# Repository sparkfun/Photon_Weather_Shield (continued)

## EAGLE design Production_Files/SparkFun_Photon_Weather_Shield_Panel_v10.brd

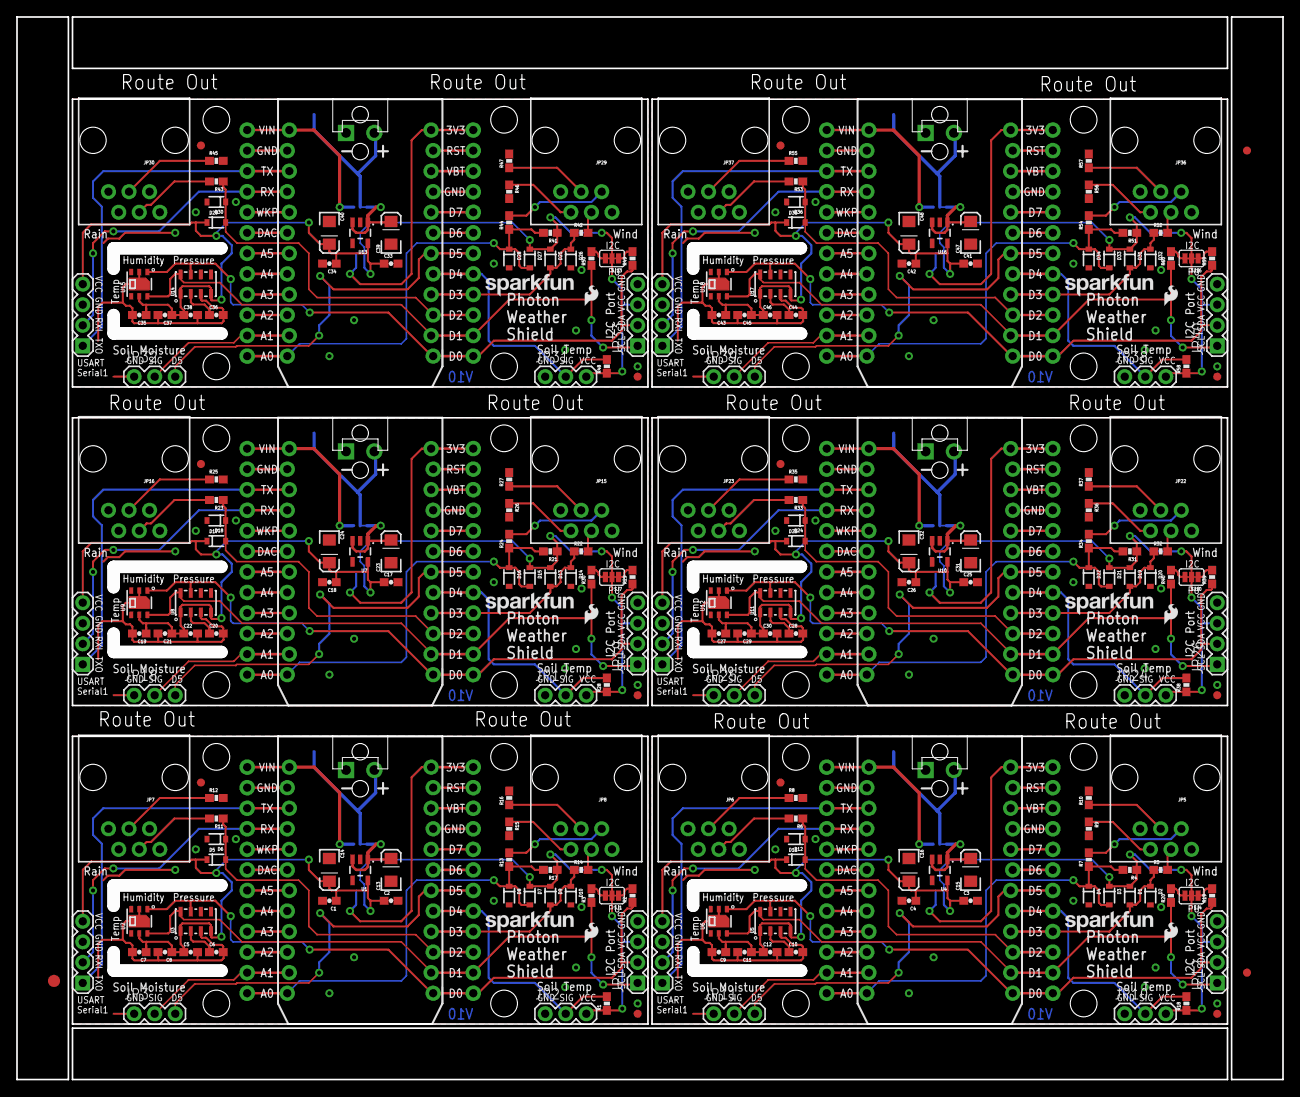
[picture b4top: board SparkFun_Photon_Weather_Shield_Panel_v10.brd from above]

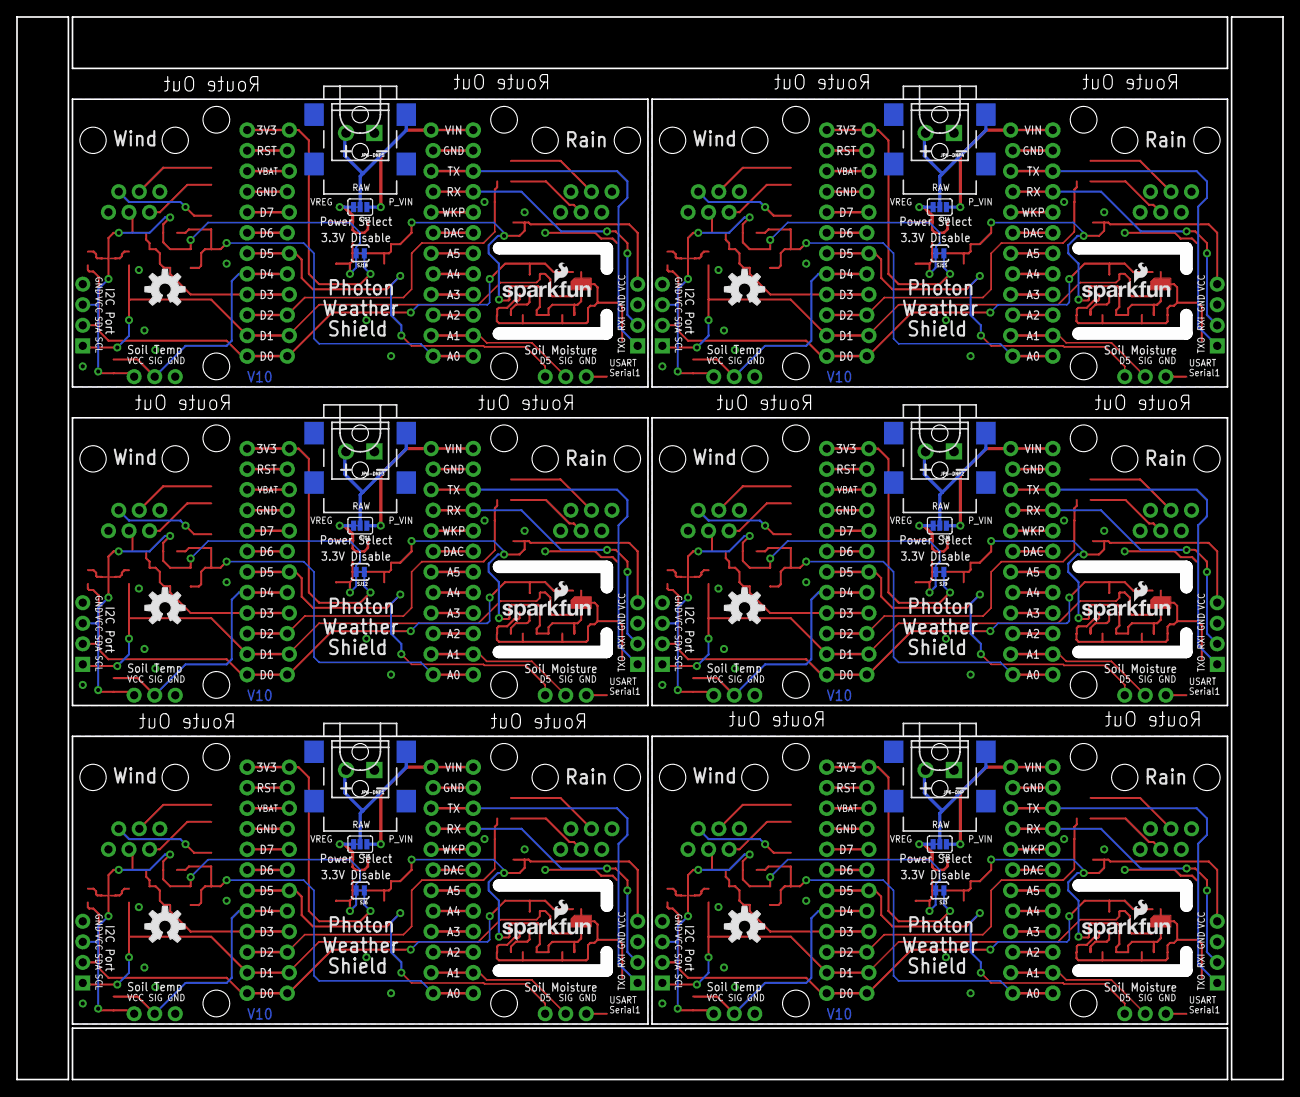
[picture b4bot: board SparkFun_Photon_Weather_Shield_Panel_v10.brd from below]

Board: 2 copper layers, 155.1 x 130.0 mm, 273 parts (36 on the bottom side), 150 nets.

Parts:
C1, C4, C8, C11, C18, C21, C26, C29, C34, C37, C42, C45: 1.0uF; 0603-CAP
C2, C3, C5, C6, C7, C9, C10, C12, C17, C19, C20, C22, C25, C27, C28, C30, C33, C35, C36, C38, C41, C43, C44, C46: 0.1uF; 0603-CAP
C13, C14, C15, C16, C23, C24, C31, C32, C39, C40, C47, C48: 10uF; EIA3216
D1, D2, D3, D4, D5, D6, D7, D8, D9, D10, D11, D12, D13, D14, D15, D16, D17, D18, D19, D20, D21, D22, D23, D24, D25, D26, D27, D28, D29, D30, D31, D32, D33, D34, D35, D36: 250mA/100V; SOD-323
E$1: FIDUCIAL-1.5X3
E$3, E$4: FIDUCIAL-1X2
FID1, FID2, FID3, FID4, FID5, FID6, FID7, FID8, FID9, FID10, FID11, FID12: FIDUCIAL1X2; FIDUCIAL-1X2
JP1, JP12, JP19, JP26, JP33, JP40: I2C Port; 1X04
JP2, JP10, JP17, JP24, JP31, JP38: Soil/Water Temp; 1X03
JP3, JP11, JP18, JP25, JP32, JP39: Soil Moisture; 1X03
JP4, JP13, JP20, JP27, JP34, JP41: Serial1 Port; 1X04
JP5, JP6, JP7, JP8, JP15, JP16, JP22, JP23, JP29, JP30, JP36, JP37: RJ11; RJ11-6
JP5-DNP, JP5-DNP1, JP5-DNP2, JP5-DNP3, JP5-DNP4, JP5-DNP5: 5.5x2.1mm Barrel; POWER_JACK_SMD
JP6-DNP, JP6-DNP1, JP6-DNP2, JP6-DNP3, JP6-DNP4, JP6-DNP5: SCREWTERMINAL-3.5MM-2
JP9, JP14, JP21, JP28, JP35, JP42: PHOTON_TEMPLATE_WIDE_LOCKING; SPARK_PHOTON_TEMPLATE_WIDE_LOCKING
LOGO1, LOGO3, LOGO5, LOGO7, LOGO9, LOGO11: OSHW-LOGOM; OSHW-LOGO-M
LOGO2, LOGO4, LOGO6, LOGO8, LOGO10, LOGO12: SFE_LOGO_NAME.1_INCH; SFE_LOGO_NAME_.1
R1, R4, R17, R18, R21, R28, R31, R38, R41, R48, R51, R58: 4.7K; 0603-RES
R2, R3, R19, R20, R29, R30, R39, R40, R49, R50, R59, R60: 10K; 0603-RES
R5, R6, R7, R8, R9, R10, R11, R12, R13, R14, R15, R16, R22, R23, R24, R25, R26, R27, R32, R33, R34, R35, R36, R37, R42, R43, R44, R45, R46, R47, R52, R53, R54, R55, R56, R57: 1K; 0603-RES
SJ1, SJ4, SJ7, SJ10, SJ13, SJ16: PAD-JUMPER-3-3OF3_NC_BY_TRACE_YES_SILK_FULL_BOX
SJ2, SJ5, SJ8, SJ11, SJ14, SJ17: PAD-JUMPER-3-2OF3_NC_BY_TRACE_YES_SILK_FULL_BOX
SJ3, SJ6, SJ9, SJ12, SJ15, SJ18: PAD-JUMPER-2-NC_BY_TRACE_YES_SILK
U1, U4, U7, U10, U13, U16: 3.3V MIC5219; SOT23-5
U2, U6, U9, U12, U15, U18: HTU21D
U3, U5, U8, U11, U14, U17: MPL3115A2LGA8; LGA8
U$1, U$2, U$5, U$7, U$9, U$11: SFE_LOGO_NAME_FLAME_.1
U$3, U$4, U$6, U$8, U$10, U$12: SFE_LOGO_FLAME_.1

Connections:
3.3V: C1.1, C2.1, C5.1, C7.1, C8.1, C14.A, D5.C, D7.C, D9.C, JP1.3, JP2.3, JP4.4, R1.1, R17.1, SJ1.2, SJ3.2, U1.5, U2.VDD, U3.1, U3.4
3.3V1: C3.1, C4.1, C9.1, C11.1, C12.1, C16.A, D1.C, D3.C, D11.C, JP10.3, JP12.3, JP13.4, R4.1, R18.1, SJ4.2, SJ6.2, U4.5, U5.1, U5.4, U6.VDD
3.3V2: C17.1, C18.1, C19.1, C21.1, C22.1, C24.A, D13.C, D15.C, D17.C, JP17.3, JP19.3, JP20.4, R21.1, R28.1, SJ7.2, SJ9.2, U7.5, U8.1, U8.4, U9.VDD
3.3V3: C25.1, C26.1, C27.1, C29.1, C30.1, C32.A, D19.C, D21.C, D23.C, JP24.3, JP26.3, JP27.4, R31.1, R38.1, SJ10.2, SJ12.2, U10.5, U11.1, U11.4, U12.VDD
3.3V4: C33.1, C34.1, C35.1, C37.1, C38.1, C40.A, D25.C, D27.C, D29.C, JP31.3, JP33.3, JP34.4, R41.1, R48.1, SJ13.2, SJ15.2, U13.5, U14.1, U14.4, U15.VDD
3.3V5: C41.1, C42.1, C43.1, C45.1, C46.1, C48.A, D31.C, D33.C, D35.C, JP38.3, JP40.3, JP41.4, R51.1, R58.1, SJ16.2, SJ18.2, U16.5, U17.1, U17.4, U18.VDD
GND: C1.2, C2.2, C5.2, C6.2, C7.2, C8.2, C13.C, C14.C, D6.A, D8.A, D10.A, JP1.4, JP2.1, JP3.1, JP4.3, JP5-DNP.GND, JP5-DNP.P$4, JP6-DNP.1, JP9.2, JP9.21, JP9.GND@0, JP9.GND@2, R12.2, R15.2, R16.2, U1.2, U2.7, U2.GND, U3.3
GND1: C3.2, C4.2, C9.2, C10.2, C11.2, C12.2, C15.C, C16.C, D2.A, D4.A, D12.A, JP5-DNP1.GND, JP5-DNP1.P$4, JP6-DNP1.1, JP10.1, JP11.1, JP12.4, JP13.3, JP14.2, JP14.21, JP14.GND@0, JP14.GND@2, R8.2, R9.2, R10.2, U4.2, U5.3, U6.7, U6.GND
GND2: C17.2, C18.2, C19.2, C20.2, C21.2, C22.2, C23.C, C24.C, D14.A, D16.A, D18.A, JP5-DNP2.GND, JP5-DNP2.P$4, JP6-DNP2.1, JP17.1, JP18.1, JP19.4, JP20.3, JP21.2, JP21.21, JP21.GND@0, JP21.GND@2, R25.2, R26.2, R27.2, U7.2, U8.3, U9.7, U9.GND
GND3: C25.2, C26.2, C27.2, C28.2, C29.2, C30.2, C31.C, C32.C, D20.A, D22.A, D24.A, JP5-DNP3.GND, JP5-DNP3.P$4, JP6-DNP3.1, JP24.1, JP25.1, JP26.4, JP27.3, JP28.2, JP28.21, JP28.GND@0, JP28.GND@2, R35.2, R36.2, R37.2, U10.2, U11.3, U12.7, U12.GND
GND4: C33.2, C34.2, C35.2, C36.2, C37.2, C38.2, C39.C, C40.C, D26.A, D28.A, D30.A, JP5-DNP4.GND, JP5-DNP4.P$4, JP6-DNP4.1, JP31.1, JP32.1, JP33.4, JP34.3, JP35.2, JP35.21, JP35.GND@0, JP35.GND@2, R45.2, R46.2, R47.2, U13.2, U14.3, U15.7, U15.GND
GND5: C41.2, C42.2, C43.2, C44.2, C45.2, C46.2, C47.C, C48.C, D32.A, D34.A, D36.A, JP5-DNP5.GND, JP5-DNP5.P$4, JP6-DNP5.1, JP38.1, JP39.1, JP40.4, JP41.3, JP42.2, JP42.21, JP42.GND@0, JP42.GND@2, R55.2, R56.2, R57.2, U16.2, U17.3, U18.7, U18.GND
unnamed: JP8.3, R14.2
unnamed: JP8.2, R13.2
unnamed: R3.2, SJ1.3
unnamed: JP7.3, R11.2
unnamed: C6.1, U3.2
unnamed: R2.2, SJ1.1
unnamed: JP9.3V3, JP9.24, SJ3.1
unnamed: C10.1, U5.2
unnamed: JP5.2, R7.2
unnamed: JP5.3, R5.2
unnamed: JP7.4, R12.1
unnamed: JP8.5, R15.1
unnamed: JP8.4, R16.1
unnamed: JP6.3, R6.2
unnamed: JP6.4, R8.1
unnamed: JP5.5, R9.1
unnamed: JP5.4, R10.1
unnamed: R20.2, SJ4.3
unnamed: R19.2, SJ4.1
unnamed: JP14.3V3, JP14.24, SJ6.1
unnamed: C20.1, U8.2
unnamed: JP15.2, R24.2
unnamed: JP15.3, R22.2
unnamed: JP16.3, R23.2
unnamed: JP16.4, R25.1
unnamed: JP15.5, R26.1
unnamed: JP15.4, R27.1
unnamed: R30.2, SJ7.3
unnamed: R29.2, SJ7.1
unnamed: JP21.3V3, JP21.24, SJ9.1
unnamed: C28.1, U11.2
unnamed: JP22.2, R34.2
unnamed: JP22.3, R32.2
unnamed: JP23.3, R33.2
unnamed: JP23.4, R35.1
unnamed: JP22.5, R36.1
unnamed: JP22.4, R37.1
unnamed: R40.2, SJ10.3
unnamed: R39.2, SJ10.1
unnamed: JP28.3V3, JP28.24, SJ12.1
unnamed: C36.1, U14.2
unnamed: JP29.2, R44.2
unnamed: JP29.3, R42.2
unnamed: JP30.3, R43.2
unnamed: JP30.4, R45.1
unnamed: JP29.5, R46.1
unnamed: JP29.4, R47.1
unnamed: R50.2, SJ13.3
unnamed: R49.2, SJ13.1
unnamed: JP35.3V3, JP35.24, SJ15.1
unnamed: C44.1, U17.2
unnamed: JP36.2, R54.2
unnamed: JP36.3, R52.2
unnamed: JP37.3, R53.2
unnamed: JP37.4, R55.1
unnamed: JP36.5, R56.1
unnamed: JP36.4, R57.1
unnamed: R60.2, SJ16.3
unnamed: R59.2, SJ16.1
unnamed: JP42.3V3, JP42.24, SJ18.1
PHOTON_VIN: JP9.1, JP9.VIN, SJ2.1
PHOTON_VIN1: JP14.1, JP14.VIN, SJ5.1
PHOTON_VIN2: JP21.1, JP21.VIN, SJ8.1
PHOTON_VIN3: JP28.1, JP28.VIN, SJ11.1
PHOTON_VIN4: JP35.1, JP35.VIN, SJ14.1
PHOTON_VIN5: JP42.1, JP42.VIN, SJ17.1
RAIN: D5.A, D6.C, JP9.15, JP9.D2, R11.1
RAIN1: D11.A, D12.C, JP14.15, JP14.D2, R6.1
RAIN6: D17.A, D18.C, JP21.15, JP21.D2, R23.1
RAIN9: D23.A, D24.C, JP28.15, JP28.D2, R33.1
RAIN12: D29.A, D30.C, JP35.15, JP35.D2, R43.1
RAIN15: D35.A, D36.C, JP42.15, JP42.D2, R53.1
RAW: JP5-DNP.VIN0, JP6-DNP.2, SJ2.2
RAW1: JP5-DNP1.VIN0, JP6-DNP1.2, SJ5.2
RAW2: JP5-DNP2.VIN0, JP6-DNP2.2, SJ8.2
RAW3: JP5-DNP3.VIN0, JP6-DNP3.2, SJ11.2
RAW4: JP5-DNP4.VIN0, JP6-DNP4.2, SJ14.2
RAW5: JP5-DNP5.VIN0, JP6-DNP5.2, SJ17.2
RXI: JP4.2, JP9.4, JP9.RX
RXI1: JP13.2, JP14.4, JP14.RX
RXI2: JP20.2, JP21.4, JP21.RX
RXI3: JP27.2, JP28.4, JP28.RX
RXI4: JP34.2, JP35.4, JP35.RX
RXI5: JP41.2, JP42.4, JP42.RX
SCL: JP1.1, JP9.14, JP9.D1, R3.1, U2.SCK, U3.8
SCL1: JP12.1, JP14.14, JP14.D1, R20.1, U5.8, U6.SCK
SCL2: JP19.1, JP21.14, JP21.D1, R30.1, U8.8, U9.SCK
SCL3: JP26.1, JP28.14, JP28.D1, R40.1, U11.8, U12.SCK
SCL4: JP33.1, JP35.14, JP35.D1, R50.1, U14.8, U15.SCK
SCL5: JP40.1, JP42.14, JP42.D1, R60.1, U17.8, U18.SCK
SDA: JP1.2, JP9.13, JP9.D0, R2.1, U2.DATA, U3.7
SDA1: JP12.2, JP14.13, JP14.D0, R19.1, U5.7, U6.DATA
SDA2: JP19.2, JP21.13, JP21.D0, R29.1, U8.7, U9.DATA
SDA3: JP26.2, JP28.13, JP28.D0, R39.1, U11.7, U12.DATA
SDA4: JP33.2, JP35.13, JP35.D0, R49.1, U14.7, U15.DATA
SDA5: JP40.2, JP42.13, JP42.D0, R59.1, U17.7, U18.DATA
SOIL_MOIST: JP3.2, JP9.11, JP9.A1
SOIL_MOIST3: JP11.2, JP14.11, JP14.A1
SOIL_MOIST4: JP18.2, JP21.11, JP21.A1
SOIL_MOIST5: JP25.2, JP28.11, JP28.A1
SOIL_MOIST6: JP32.2, JP35.11, JP35.A1
SOIL_MOIST7: JP39.2, JP42.11, JP42.A1
SOIL_MOIST_POWER: JP3.3, JP9.18, JP9.D5
SOIL_MOIST_POWER1: JP11.3, JP14.18, JP14.D5
SOIL_MOIST_POWER2: JP18.3, JP21.18, JP21.D5
SOIL_MOIST_POWER3: JP25.3, JP28.18, JP28.D5
SOIL_MOIST_POWER4: JP32.3, JP35.18, JP35.D5
SOIL_MOIST_POWER5: JP39.3, JP42.18, JP42.D5
SOIL_TEMP: JP2.2, JP9.17, JP9.D4, R1.2
SOIL_TEMP2: JP10.2, JP14.17, JP14.D4, R18.2
SOIL_TEMP3: JP17.2, JP21.17, JP21.D4, R28.2
SOIL_TEMP4: JP24.2, JP28.17, JP28.D4, R38.2
SOIL_TEMP5: JP31.2, JP35.17, JP35.D4, R48.2
SOIL_TEMP6: JP38.2, JP42.17, JP42.D4, R58.2
TXO: JP4.1, JP9.3, JP9.TX
TXO1: JP13.1, JP14.3, JP14.TX
TXO2: JP20.1, JP21.3, JP21.TX
TXO3: JP27.1, JP28.3, JP28.TX
TXO4: JP34.1, JP35.3, JP35.TX
TXO5: JP41.1, JP42.3, JP42.TX
VREG: C13.A, SJ2.3, U1.1, U1.3
VREG1: C15.A, SJ5.3, U4.1, U4.3
VREG2: C23.A, SJ8.3, U7.1, U7.3
VREG3: C31.A, SJ11.3, U10.1, U10.3
VREG4: C39.A, SJ14.3, U13.1, U13.3
VREG5: C47.A, SJ17.3, U16.1, U16.3
WDIR: D7.A, D8.C, JP9.12, JP9.A0, R13.1, R17.2
WDIR1: D3.A, D4.C, JP14.12, JP14.A0, R4.2, R7.1
WDIR2: D15.A, D16.C, JP21.12, JP21.A0, R21.2, R24.1
WDIR3: D21.A, D22.C, JP28.12, JP28.A0, R31.2, R34.1
WDIR4: D27.A, D28.C, JP35.12, JP35.A0, R41.2, R44.1
WDIR5: D33.A, D34.C, JP42.12, JP42.A0, R51.2, R54.1
WSPEED: D9.A, D10.C, JP9.16, JP9.D3, R14.1
WSPEED1: D1.A, D2.C, JP14.16, JP14.D3, R5.1
WSPEED2: D13.A, D14.C, JP21.16, JP21.D3, R22.1
WSPEED3: D19.A, D20.C, JP28.16, JP28.D3, R32.1
WSPEED4: D25.A, D26.C, JP35.16, JP35.D3, R42.1
WSPEED5: D31.A, D32.C, JP42.16, JP42.D3, R52.1

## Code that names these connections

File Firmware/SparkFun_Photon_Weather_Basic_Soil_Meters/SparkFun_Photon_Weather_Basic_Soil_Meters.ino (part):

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OneWire oneWire(ONE_WIRE_BUS);
DallasTemperature sensors(&oneWire);

#define SOIL_MOIST A1
#define SOIL_MOIST_POWER D5

int WDIR = A0;
int RAIN = D2;
int WSPEED = D3;

//Run I2C Scanner to get address of DS18B20(s)
//(found in the Firmware folder in the Photon Weather Shield Repo)
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int winddir_avg2m = 0; // [0-360 2 minute average wind direction]
float windgustmph_10m = 0; // [mph past 10 minutes wind gust mph ]
int windgustdir_10m = 0; // [0-360 past 10 minutes wind gust direction]
float rainin = 0; // [rain inches over the past hour)] -- the accumulated rainfall in the past 60 min
long lastWindCheck = 0;
volatile float dailyrainin = 0; // [rain inches so far today in local time]

float humidity = 0;
float tempf = 0;
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    sensors.begin();
    sensors.setResolution(inSoilThermometer, TEMPERATURE_PRECISION);

    pinMode(WSPEED, INPUT_PULLUP); // input from wind meters windspeed sensor
    pinMode(RAIN, INPUT_PULLUP); // input from wind meters rain gauge sensor

    pinMode(SOIL_MOIST_POWER, OUTPUT);//power control for soil moisture
    digitalWrite(SOIL_MOIST_POWER, LOW);//Leave off by defualt

    Serial.begin(9600);   // open serial over USB
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
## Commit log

2015-02-23 Adding Hardware Files
    Adding Hardware Files
2015-03-13 Adding I2C header
    Adding I2C header to connect any I2C peripherals desired to enhance the
    weather station.
2015-03-20 Major Routing - Close to Proto
    Major Routing - Close to Proto. added lots of silk and jumper features.
    Finished routing.
2015-03-20 Final touches before peer review
    Ran my own QC checklist and fixed a few minor details such as
    fiducials, labeling, more rerouting, etc.
2015-03-20 Renaming
    Renaming files and folders to remove Spark name.
2015-03-20 Peer Review complete
    Peer review with Jim, added 3.3V disable jumper for two power sources
    at once (debugging), minor edits.
2015-03-20 Peer Review complete
    Peer Review complete
2015-03-23 Ready for QC Checklist
    Replaced all old Eagle parts with most up to date library parts, added
    a Dimension Route as well as the Milling Route, Fixed Trestrict and
    Restrict, which were on Keepout instead.
2015-03-23 Ready for QC Checklist
    Replaced all old Eagle parts with most up to date library parts, added
    a Dimension Route as well as the Milling Route, Fixed Trestrict and
    Brestrict, which were on Keepout instead.
2015-03-24 QC Checklist Issues Addressed
    QC Checklist Issues Addressed: added PROD_IDs to few missing parts,
    changed Y junctions to T junctions, fixed pin 1 markings, added Values
    where needed.
2015-03-24 Added DNP to a few connectors
    Added DNP to a few connectors that I missed and do not need to be
    populated.
2015-03-25 Ready for Protos
    Moved Soil_Moisture from A2 to A1 and deleted unused Light net on A1.
2015-04-03 Changed Name
    Changed silk to new name: Weather Shield for Photon
2015-04-03 Changed name
    Fixed silk on back too!!!
2015-05-22 Ready for Reds
    Added USART port, changed soil moisture vcc to D5, minor silk and route
    changes.
2015-05-26 Ready for last QC Check
    Most recent changes pushed to github include
    -Locking Footprint added to Photon Template for selective soldering
    -updating Photon template to wider version for selective solder
    -breakout USART port
    -changing power on Soil Moisture from Vcc to D5
    -Minor route and silk changes.
2015-05-28 Ready for Reds
    Ready for Reds
2015-05-28 created panel v10
2015-05-28 re-do, added more "route out" for GP
2015-06-29 Adding Firmware folder, libraries and examples
    Adding the Firmware folder which contains the necessary libraries and
    example sketches needed to use the weather shield.
2015-06-29 Adding Firmware examples
    Adding Photon Weather Shield Firmware examples.
2015-06-30 Firmware updates
    Firmware updates
2015-06-30 Firmware update
    Firmware update
2015-07-02 Updating Example Sketches
    Updating Example Sketches
2015-07-03 Updating LCD Example
2015-07-03 Firmware updates
2015-07-03 Update Comments
2015-07-22 Added Example code to upload to Weather Underground
    Added Example code to upload to Weather Underground
    Also added dew point calculation, which meant running
    fahrenheit/celsius vars, the dew point calculation wants C.
    Also added deep sleep to shut everything down between sends, to help
    folks using batteries.
2015-07-22 Update SparkFun_Photon_Weather_Wunderground.ino
    Updated header description text
2015-07-28 Added a delay before sleep
    The photon was going to sleep before the message was sent to
    wunderground, adding the delay before sleep ensures that the data makes
    it’s way over.
2015-07-28 Eliminated two sensor read requests
    Converted temps instead of making additional sensor reads. Save a tiny
    bit of time, save a tiny bit of power.
2015-08-20 Updated all examples to use new Weather Shield Lib
    Also added more comments and revised the altitude/barometer sections.
2015-08-21 Major overhaul on examples using new library
    Major overhaul on examples using new library
2015-08-25 Pull the send to weather underground out of the main loop
    Pull the send to Weather Underground out of the main loop and get it in
    a function. For consistency and cleanliness.
2015-08-27 Moved Route out note to dimension layer
    Moved Route out note to dimension layer to match production files.
2015-09-01 Updated to most recent libraries (Phant & OneWire)
    Updated all examples to the most recent version os the Phant and
    OneWire Particle Libraries. Updated a few comments.
2015-10-27 Initial Commit to V11
2016-01-04 Updated README.md to indicate reason for the fork
2016-01-05 New standalone SparkFunPhant module with improved transfer loop
2016-03-02 Adding Simple Phant example
    Adding simpler Phant example for those who do not have extra sensors
    attached. Minor text cleanup.
2016-08-25 Preliminary Checklist review
2016-09-17 Initial fork for additional sensors
    This fork of Sparkfun’s Photon Weather shield is intended to build upon
    the basic code with support for some customized sensors.
2016-11-01 Final Changes before ENG Checklist
    Many minor changes: text, font, paste under Si7021 footprint. correct
    layers for info.
2016-11-01 Updates for ENG Checklist
2016-11-01 Rwady for ENG Chekclist
2016-11-01 Adding units to Measure layer
2016-11-08 Pushing fixes to first round ENG checklist
    fixed exposed traces from TSTOP and added TSTOP to Si7021 IC footprint
    and updated on this board.
2016-11-30 Fixed silk for UART Serial1
2016-11-30 Fixed silk on back of Board
    USART -> UART
2016-12-05 Changed silk SIG to pin names on soil ports.
2016-12-09 Final ENG_Checklist before ordering REDs
    Fixed two issues: misspelling and overlapping values on nets.. Pushing
    for Reds.
2016-12-09 Final ENG_Checklist before ordering REDs
    Final ENG_Checklist before ordering REDs
2016-12-15 panel
2017-03-22 Fixed GET syntax
    Fixed GET syntax (added HTTP and r\n\r\n)
    Also - added listener to print the server response to serial for
    debugging
2017-03-22 Reduced server response wait time
    On the particle core long delays can impact the wifi connection
    reliability
2017-03-22 Cleanup
    cleanup debug notes
2018-06-05 Update w/ Correct Voltage Regulator Name
    The schematic was updated incorrectly with the voltage regulator name and specifications. Instead of the MIC5219, it is populated with the **MIC5205**.
    While the recommended operating voltage from the [datasheet](http://ww1.microchip.com/downloads/en/DeviceDoc/20005785A.pdf) is up to +16V, the actual stable voltage in real world conditions is actual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
2023-06-28 Retire Product
